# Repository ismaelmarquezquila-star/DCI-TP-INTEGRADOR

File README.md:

## Trabajo práctico final de la asignatura DCI ##
Este repositorio contiene el trabajo práctico final para la asignatura de Diseño de Circuitos Impresos de la carrera de posgrado de FIUBA.

* Autor: Ismael Farid Marquez Quila
* Título corto del trabajo:  Shield_Datalogger
* Descripción: Placa tipo Shield de 2 capas compatible con placas STM32 Nucleo-64 (conectores Morpho) que consolida un sensor inercial IMU de 6 ejes (LSM6DS3 mediante bus I2C) y un zócalo lector de tarjetas MicroSD (mediante bus SPI) en un único circuito impreso compacto. Su objetivo es la adquisición y almacenamiento local de datos inerciales (datalogger) operando a 3,3 V, diseñado bajo criterios de integridad de señal (plano de tierra continuo GND en la cara inferior, capacitores de desacoplamiento locales, pistas de 0,15 mm para señales y 0,51 mm para alimentación) y encapsulados SMD 0805 aptos para soldadura manual.
* Cursada: OCT-NOV-DIC 2026

## Licencia de este trabajo ##
Este diseño de hardware abierto se publica bajo la licencia **CERN Open Hardware Licence Version 2 - Permissive (CERN-OHL-P-2.0)**, siguiendo las recomendaciones de la Open Source Hardware Association (OSHWA).

## Estructura del TP FINAL ##

Se propone y se pide utilizar la siguiente estructura.

* doc: Toda la información sobre el circuito, principalmente de autoría o procesamiento propio. Por ejemplo:
  * Notas de ingeniería propias.
  * Notas de aplicación propias.
  * Estudios previos, estado del arte, resumen de las investigaciones.
  * Notas con cálculos.
  * Dibujos adicionales.
  * Fotos de los prototipos.
  * Presupuestos, cotizaciones.
* info: Toda la iformación recolectada, principalmente de terceros, como por ejemplo:
  * Hojas de datos.
  * Notas de aplicación.
  * Info de productos comerciales.
  * Info en internet.
* pcb: Archivos de diseño esquemático y pcb.

Dependiendo la magnitud del proyecto, tendremos más o menos información en estos directorios. 
Revisar los README.md en cada directorio para conocer las pautas de cada uno para este TP.

NOTA: El alumno puede y debe borrar de este archivo todo lo que considere necesario, por ejemplo las aclaraciones del docente y esta misma nota.

## Obligatorios para el TP Final ##
* doc/propuesta/README.md (con textos y links, formato markdown, a imágenes que deben estar en el mismo repo. Las imágenes son las que se piden en las pautas de TP).
* info/*.pdf (Se piden solo las hojas de datos de los componentes relevantes como circuitos integrados, conectores particulares, módulos, etc. No es necesario poner hojas de pasivos, discretos comunes, conectores estándar.)
* pcb/* (Acá va el proyecto KiCad, modelos 3D, bibliotecas particulares y archivos generados como BOM, gerbers, etc.). EVITE subir al git archivos temporales de KiCad. Se recomienda usar un .gitignore adecuado.
* El alumnos es libre de agregar otras cosas, pero siempre tenga en cuenta que el repositorio es público. Evitar colocar información personal o documentación confidencial.

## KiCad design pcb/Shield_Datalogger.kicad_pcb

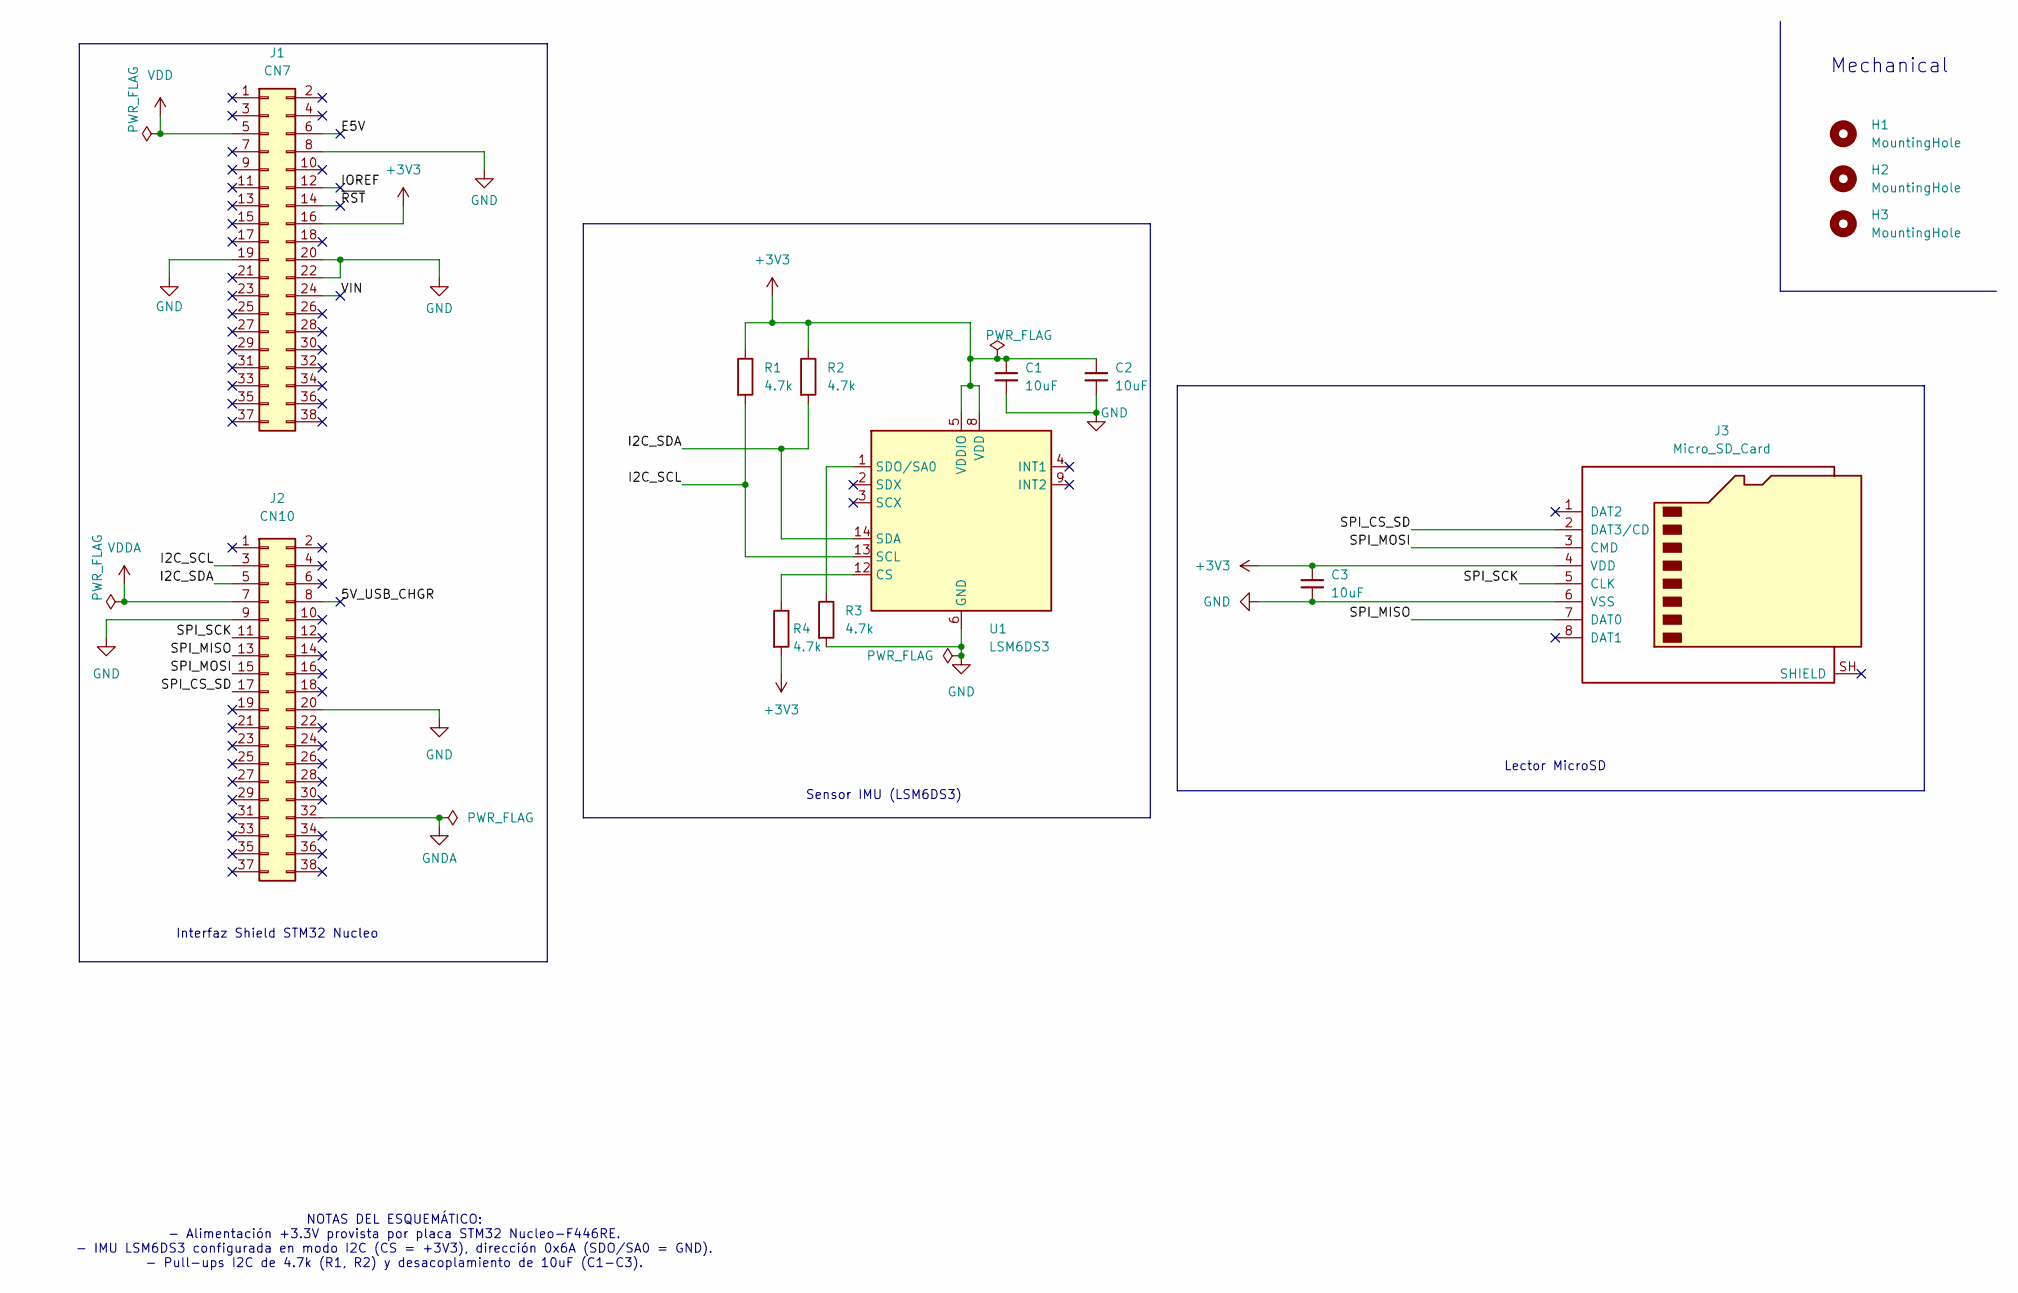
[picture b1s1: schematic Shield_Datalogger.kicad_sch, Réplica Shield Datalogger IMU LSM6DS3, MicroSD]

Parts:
C1, C2, C3: 10uF; C_0805_2012Metric
H1, H2, H3: MountingHole; MountingHole_3.2mm_M3
J1: CN7; PinSocket_2x19_P2.54mm_Vertical
J2: CN10; PinSocket_2x19_P2.54mm_Vertical
J3: Micro_SD_Card; microSD_HC_Hirose_DM3AT-SF-PEJM5
R1, R2, R3, R4: 4.7k; R_0805_2012Metric
U1: LSM6DS3; LGA-14_3x2.5mm_P0.5mm_LayoutBorder3x4y

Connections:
+3V3: C1.2, C2.2, C3.1, J1.16, J3.4 (VDD), R1.1, R2.1, R4.2, U1.5 (VDDIO), U1.8 (VDD)
/5V_USB_CHGR: J2.8
/E5V: J1.6
/I2C_SCL: J2.3, R1.2, U1.13 (SCL)
/I2C_SDA: J2.5, R2.2, U1.14 (SDA)
/IOREF: J1.12
/SPI_CS_SD: J2.17, J3.2 (DAT3/CD)
/SPI_MISO: J2.13, J3.7 (DAT0)
/SPI_MOSI: J2.15, J3.3 (CMD)
/SPI_SCK: J2.11, J3.5 (CLK)
/VIN: J1.24
/~RST: J1.14
GND: C1.1, C2.1, C3.2, J1.8, J1.19, J1.20, J1.22, J2.9, J2.20, J3.6 (VSS), R3.2, U1.6 (GND), U1.7 (GND)
GNDA: J2.32
unnamed: R4.1, U1.12 (CS)
unnamed: R3.1, U1.1 (SDO/SA0)
VDD: J1.5
VDDA: J2.7

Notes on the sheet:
Interfaz Shield STM32 Nucleo
Mechanical
NOTAS DEL ESQUEMÁTICO: - Alimentación +3.3V provista por placa STM32 Nucleo-F446RE. - IMU LSM6DS3 configurada en modo I2C (CS = +3V3), dirección 0x6A (SDO/SA0 = GND). - Pull-ups I2C de 4.7k (R1, R2) y desacoplamiento de 10uF (C1-C3).
Sensor IMU (LSM6DS3)
Lector MicroSD

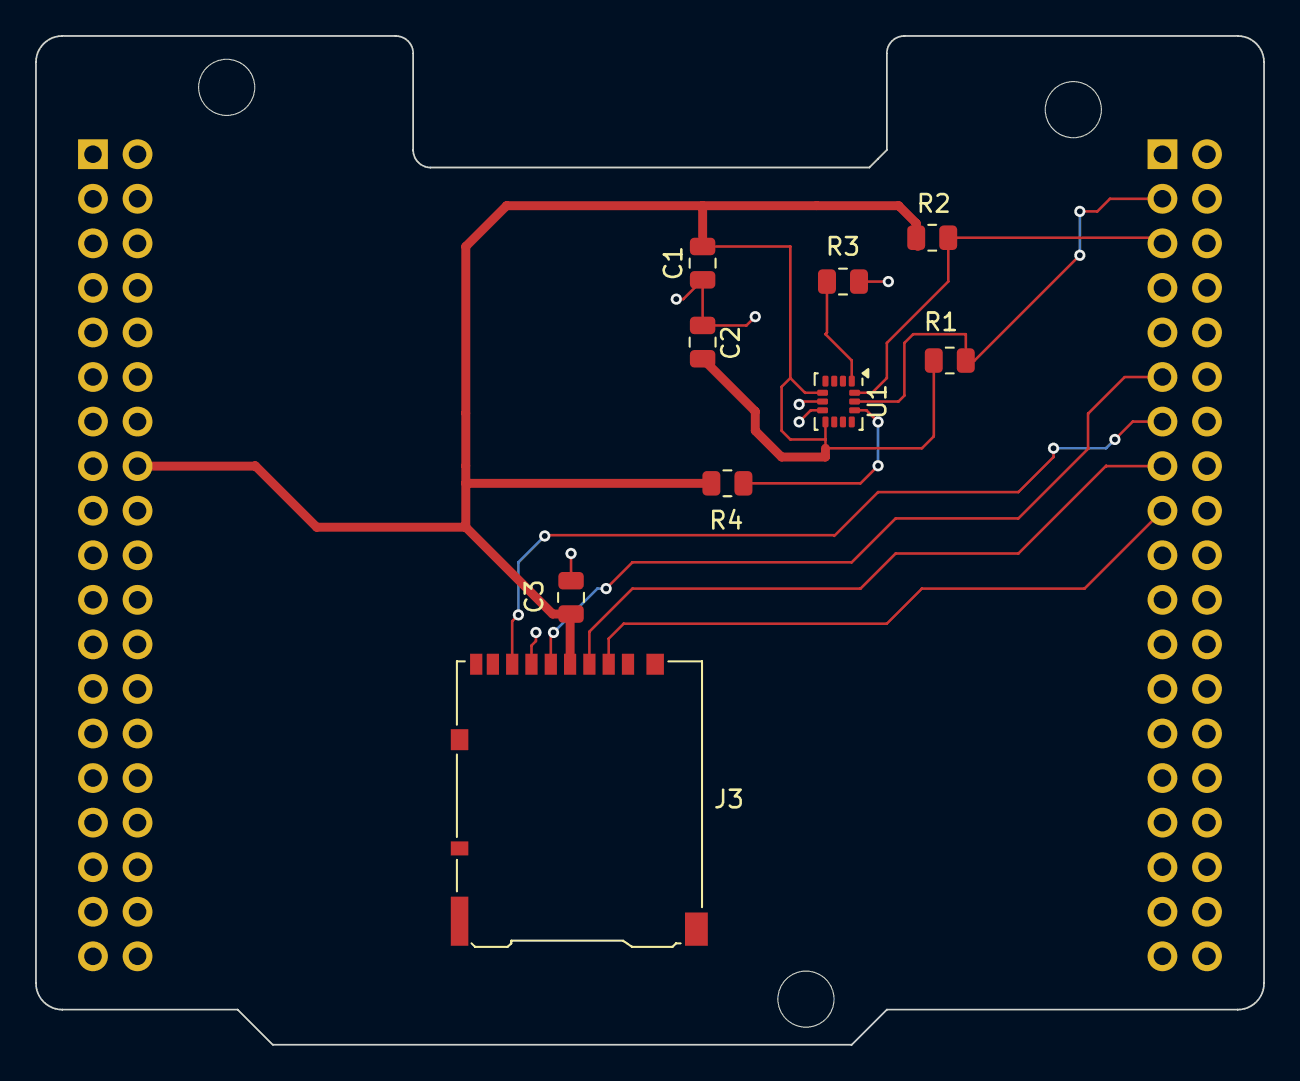
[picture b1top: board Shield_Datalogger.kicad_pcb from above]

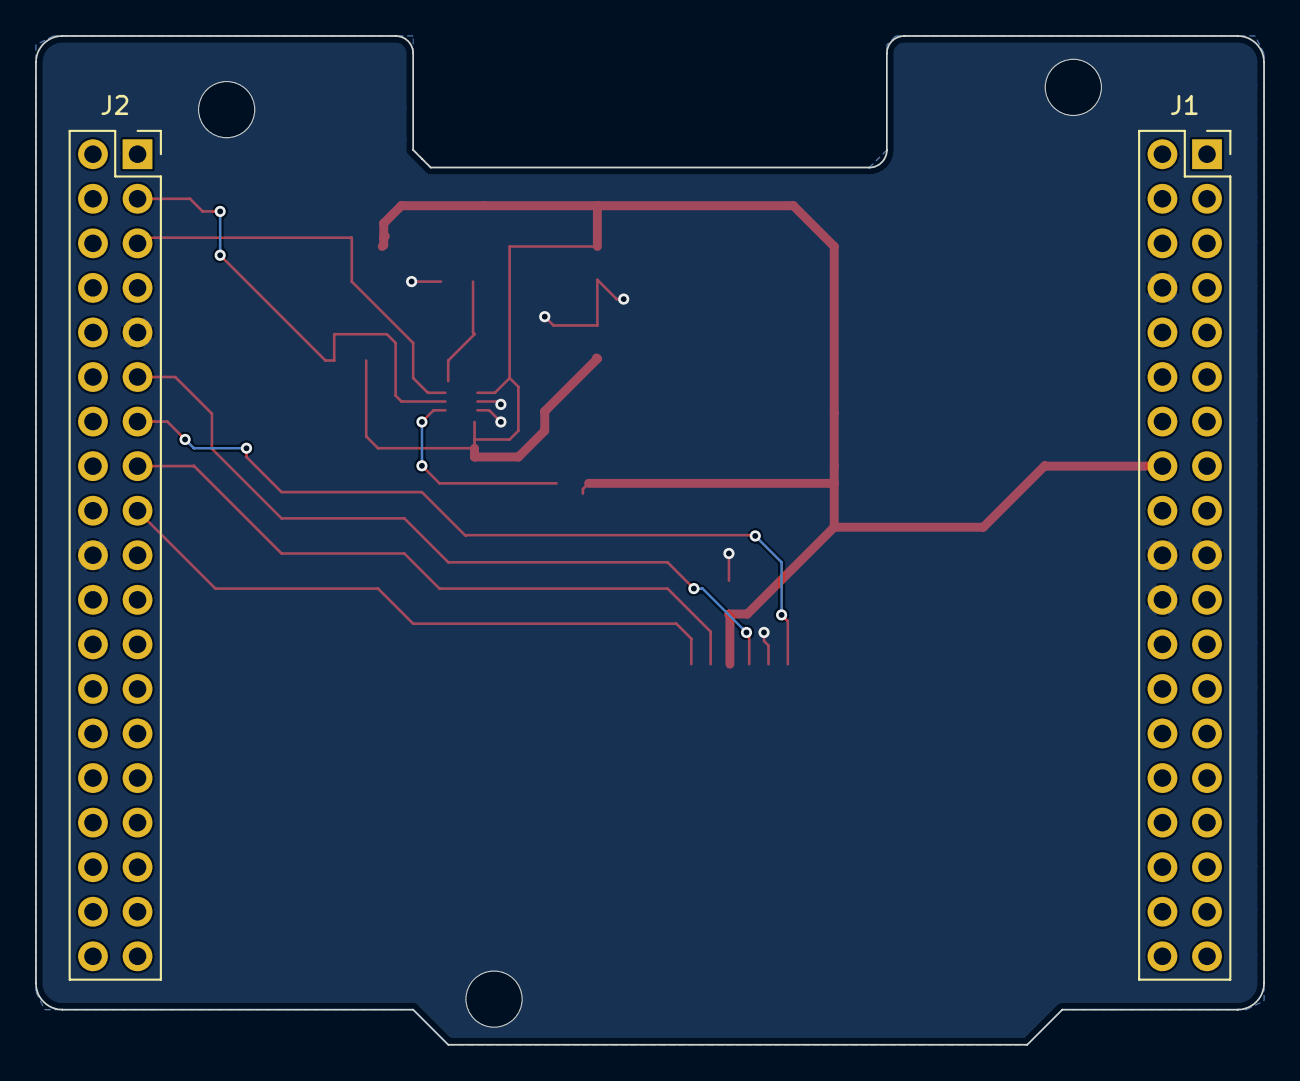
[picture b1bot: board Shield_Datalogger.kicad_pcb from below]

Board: 2 copper layers, 70.0 x 57.5 mm, 14 parts (2 on the bottom side), 10 nets.

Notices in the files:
pcb/Shield_Datalogger.kicad_sch:
Licencia: CC BY 4.0
